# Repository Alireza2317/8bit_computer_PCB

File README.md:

# PCB Design of Ben Eater's 8-Bit Computer 🖥️

A complete **Printed Circuit Board (PCB)** implementation of the famous 8-bit computer architecture (SAP-1) designed by Ben Eater.

Moving from breadboards to a production-ready PCB, this project demonstrates complex signal routing, hierarchical schematic organization, and digital logic design using the **74xx TTL series** chips.

## 📸 3D Render

## ⚙️ Technical Specifications
| Feature | Details |
| :--- | :--- |
| **EDA Software** | KiCad |
| **Architecture** | Simple As Possible |
| **Logic Family** | 74LS / 74HC Series (TTL) |
| **PCB Layers** | 2 Layers |
| **Mounting** | Through-Hole Technology (THT) |

## 🧠 Design Challenges & Features
* **Hierarchical Schematics:** The design is broken down into modular logical blocks (Clock, RAM, ALU, Control Logic) using KiCad's hierarchical sheets for maintainability.
* **Complex Routing:** Managing hundreds of data and control lines on a 2-layer board required careful optimization of trace paths to minimize vias and ensure signal integrity.
* **Bus Architecture:** Implements a central 8-bit bus connecting all registers and the Arithmetic Logic Unit.

## 🖼️ Gallery

#### PCB Layout

#### 3d View Snapshot

### Schematics (Sneak Peek)

#### Root schematic page

#### RAM Module

## 🚀 How to Open
1. **Clone the repository:**
   ```bash
   git clone https://github.com/Alireza2317/8bit_computer_PCB
   ```
2. **Open in KiCad:**
   * Launch **KiCad**.
   * Go to `File > Open Project`.
   * Select the `.kicad_pro` file in the root directory.
3. **Explore:**
   * Click the **Schematic Editor** to see the logic.
   * Click the **PCB Editor** to see the physical routing.

## 👏 Acknowledgments
This project is based on the incredible educational series by **Ben Eater**.
* [Ben Eater's Website](https://eater.net/8bit)
* [YouTube Playlist](https://www.youtube.com/playlist?list=PLowKtXNTBypGqImE405J2565dvjafglHU)

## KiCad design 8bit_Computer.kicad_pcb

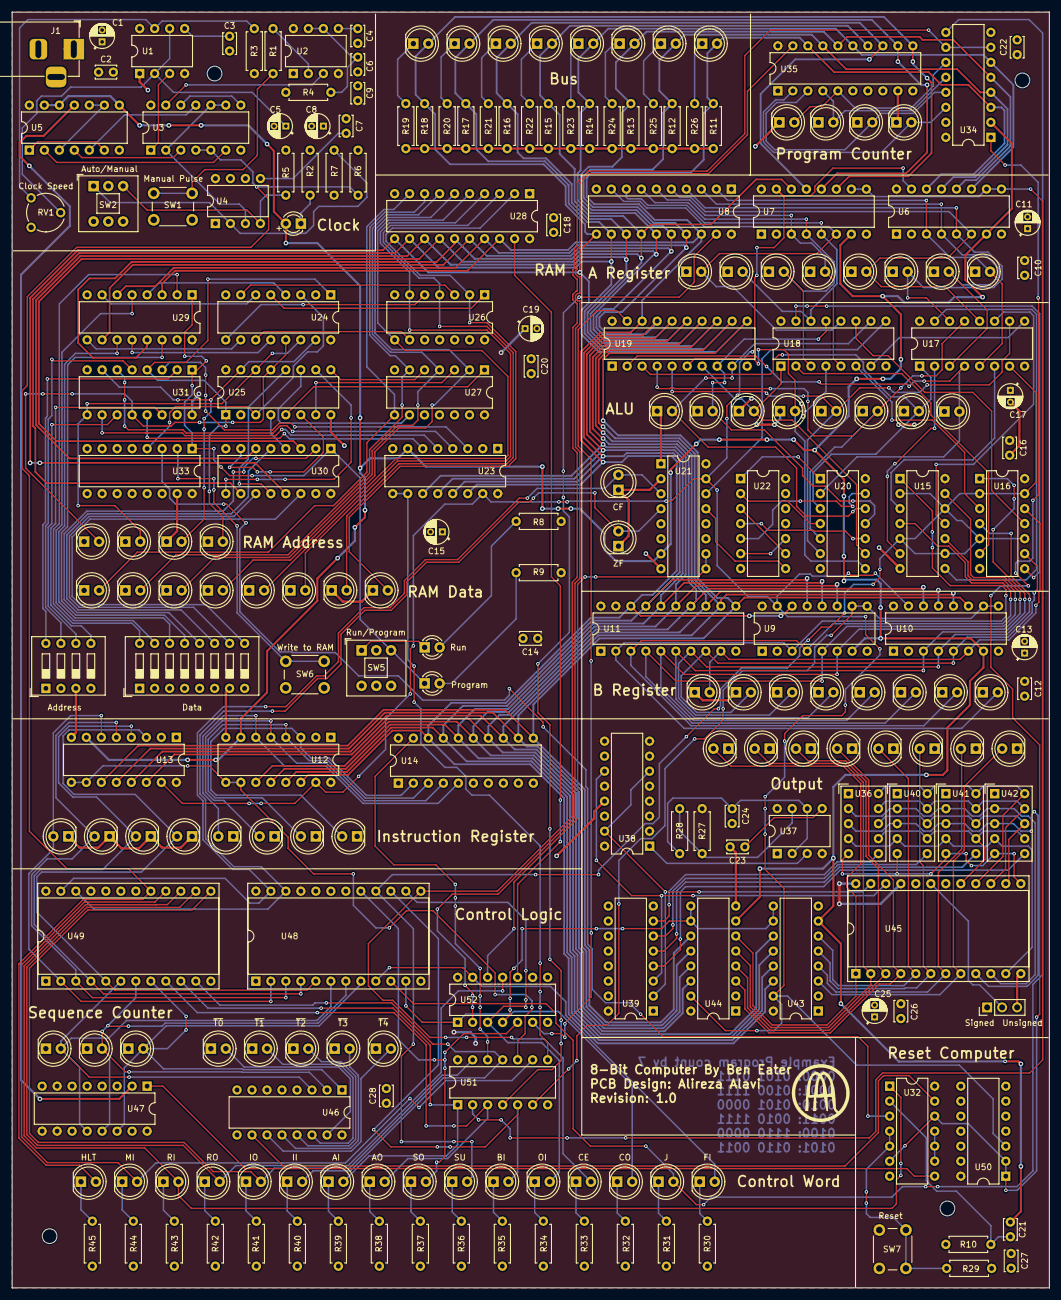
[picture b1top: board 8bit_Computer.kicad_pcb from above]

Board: 2 copper layers, 175.6 x 216.0 mm, 232 parts (0 on the bottom side), 231 nets.

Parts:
C1, C5: 100nF; CP_Radial_D4.0mm_P2.00mm
C2, C9, C14, C16, C18, C21: 1uF; C_Disc_D3.4mm_W2.1mm_P2.50mm
C3, C4, C7, C10, C12, C20, C22, C23, C24, C26, C27, C28: 10nF; C_Disc_D3.4mm_W2.1mm_P2.50mm
C6: 100nF; C_Disc_D3.4mm_W2.1mm_P2.50mm
C8: 2.2uF; CP_Radial_D4.0mm_P2.00mm
C11, C15, C17, C19: 10nF; CP_Radial_D4.0mm_P2.00mm
C13, C25: 1uF; CP_Radial_D4.0mm_P2.00mm
D1: bus7; LED_D3.0mm
D2: bus6; LED_D5.0mm
D3: bus5; LED_D5.0mm
D4: bus4; LED_D5.0mm
D5: bus3; LED_D5.0mm
D6: bus2; LED_D5.0mm
D7: bus1; LED_D5.0mm
D8: bus0; LED_D5.0mm
D9: pc3; LED_D5.0mm
D10: pc2; LED_D5.0mm
D11: pc1; LED_D5.0mm
D12: pc0; LED_D5.0mm
D13: Clock LED; LED_D5.0mm
D14: a7; LED_D5.0mm
D15: a6; LED_D5.0mm
D16: a5; LED_D5.0mm
D17: a4; LED_D5.0mm
D18: a3; LED_D5.0mm
D19: a2; LED_D5.0mm
D20: a0; LED_D5.0mm
D21: a1; LED_D5.0mm
D22: s7; LED_D5.0mm
D23: s5; LED_D5.0mm
D24: s6; LED_D5.0mm
D25: s4; LED_D5.0mm
D26: s3; LED_D5.0mm
D27: s2; LED_D5.0mm
D28: s1; LED_D5.0mm
D29: s0; LED_D5.0mm
D30: CF; LED_D5.0mm
D31: ra3; LED_D5.0mm
D32: ra2; LED_D5.0mm
D33: ra0; LED_D5.0mm
D34: ra1; LED_D5.0mm
D35: ZF; LED_D5.0mm
D36: r7; LED_D5.0mm
D37: r6; LED_D5.0mm
D38: r4; LED_D5.0mm
D39: r5; LED_D5.0mm
D40: r3; LED_D5.0mm
D41: r2; LED_D5.0mm
D42: r0; LED_D5.0mm
D43: r1; LED_D5.0mm
D44: Run; LED_D5.0mm
D45: Program; LED_D5.0mm
D46: b6; LED_D5.0mm
D47: b7; LED_D5.0mm
D48: b5; LED_D3.0mm
D49: b4; LED_D3.0mm
D50: b2; LED_D5.0mm
D51: b3; LED_D5.0mm
D52: b0; LED_D5.0mm
D53: b1; LED_D5.0mm
D54: out7; LED_D5.0mm
D55: out6; LED_D5.0mm
D56: out5; LED_D5.0mm
D57: out3; LED_D5.0mm
D58: out4; LED_D5.0mm
D59: out2; LED_D5.0mm
D60: out1; LED_D5.0mm
D61: out0; LED_D5.0mm
D62: ir7; LED_D5.0mm
D63: ir6; LED_D5.0mm
D64: ir5; LED_D5.0mm
D65: ir3; LED_D5.0mm
D66: ir4; LED_D5.0mm
D67: ir2; LED_D5.0mm
D68: ir1; LED_D5.0mm
D69: ir0; LED_D5.0mm
D70: sc1; LED_D5.0mm
D71: sc2; LED_D5.0mm
D72: sc0; LED_D5.0mm
D73: T0; LED_D5.0mm
D74: T2; LED_D5.0mm
D75: T1; LED_D5.0mm
D76: T4; LED_D5.0mm
D77: T3; LED_D5.0mm
D78: HLT; LED_D5.0mm
D79: MAR_In; LED_D5.0mm
D80: RAM_In; LED_D5.0mm
D81: RAM_Out; LED_D5.0mm
D82: IR_Out; LED_D5.0mm
D83: IR_In; LED_D5.0mm
D84: A_Out; LED_D5.0mm
D85: A_In; LED_D5.0mm
D86: Sum_Out; LED_D5.0mm
D87: Subtract; LED_D5.0mm
D88: Out_In; LED_D5.0mm
D89: B_In; LED_D5.0mm
D90: PC_En; LED_D5.0mm
D91: PC_Out; LED_D5.0mm
D92: Jump; LED_D5.0mm
D93: Flags_In; LED_D5.0mm
J1: DC Input; BarrelJack_Horizontal
J2: Sign Mode Jumper; PinHeader_1x03_P2.54mm_Vertical
M1, M2, M3, M4: MountingHole_2.5mm
R1, R3, R20, R22, R27: 1K; R_Axial_DIN0207_L6.3mm_D2.5mm_P7.62mm_Horizontal
R2: 1M; R_Axial_DIN0207_L6.3mm_D2.5mm_P7.62mm_Horizontal
R4, R5, R7, R9, R11, R13, R16, R19: 100; R_Axial_DIN0207_L6.3mm_D2.5mm_P7.62mm_Horizontal
R6, R8, R10, R12, R14, R15, R17, R18, R23, R44: 10K; R_Axial_DIN0207_L6.3mm_D2.5mm_P7.62mm_Horizontal
R21, R24, R25, R28, R29, R30, R31, R32, R33, R34, R35, R36, R37, R38, R39, R40, R41, R42, R43: 330; R_Axial_DIN0207_L6.3mm_D2.5mm_P7.62mm_Horizontal
R26: 100K; R_Axial_DIN0207_L6.3mm_D2.5mm_P7.62mm_Horizontal
R45: 1k; R_Axial_DIN0207_L6.3mm_D2.5mm_P7.62mm_Horizontal
RV1: 100K; Potentiometer_Piher_PT-6-V_Vertical
SW1: Clock Mode Switch; SW_PUSH_6mm
SW2: Manual Pulse; SW_Push_2P2T_Toggle_CK_PVA2OAH5xxxxxxV2
SW3: Program Address; SW_DIP_SPSTx04_Slide_9.78x12.34mm_W7.62mm_P2.54mm
SW4: Program Data; SW_DIP_SPSTx08_Slide_9.78x22.5mm_W7.62mm_P2.54mm
SW5: Program Button; SW_Push_2P2T_Toggle_CK_PVA2OAH5xxxxxxV2
SW6: Program/Run Mode Switch; SW_PUSH_6mm
SW7: Reset Button; SW_PUSH_6mm
U1, U2: NE555P; DIP-8_W7.62mm
U3: 74LS245; DIP-14_W7.62mm
U4: 74LS00; DIP-8_W7.62mm
U5, U50, U52: 74LS00; DIP-14_W7.62mm
U6, U9, U18, U29, U34: 74LS245; DIP-16_W7.62mm
U7, U47: 74LS161; DIP-16_W7.62mm
U8: NE555P; DIP-20_W7.62mm
U10, U23, U24, U30, U31, U33, U44: 74LS173; DIP-16_W7.62mm
U11: 74LS173; DIP-20_W7.62mm
U12, U21: 74LS157; DIP-16_W7.62mm
U13: 74LS189; DIP-16_W7.62mm
U14: 74LS04; DIP-20_W7.62mm
U15: 74LS189; DIP-14_W7.62mm
U16, U22: 74LS157; DIP-14_W7.62mm
U17: 74LS04; DIP-16_W7.62mm
U19: 74LS283; DIP-20_W7.62mm
U20: 74LS283; DIP-14_W7.62mm
U25: 74LS08; DIP-16_W7.62mm
U26: 74LS02; DIP-14_W7.62mm
U27: 74LS86; DIP-14_W7.62mm
U28: 74LS86; DIP-20_W7.62mm
U32: 74LS173; DIP-14_W7.62mm
U35: 74LS76; DIP-20_W7.62mm
U36: NE555D; HDSP-7401
U37: Hundred's Place; DIP-8_W7.62mm
U38: Minus Sign; DIP-16_W7.62mm
U39: Ten's Place; DIP-16_W7.62mm
U40: One's Place; HDSP-7401
U41, U42: 28c16; HDSP-7401
U43: 74LS139; DIP-16_W7.62mm
U45: 74LS173; DIP-24_W15.24mm_Socket
U46: 28c16; DIP-16_W7.62mm
U48: 74LS138; DIP-24_W15.24mm_Socket
U49: 74LS06; DIP-24_W15.24mm_Socket
U51: 74LS06; DIP-14_W7.62mm

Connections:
/A Register/a0: D9.2 (A), U6.3 (Q0), U8.2 (A0), U17.5 (A1)
/A Register/a1: D8.2 (A), U6.4 (Q1), U8.3 (A1), U17.3 (A2)
/A Register/a2: D7.2 (A), U6.5 (Q2), U8.4 (A2), U17.14 (A3)
/A Register/a3: D6.2 (A), U6.6 (Q3), U8.5 (A3), U17.12 (A4)
/A Register/a4: D5.2 (A), U7.3 (Q0), U8.6 (A4), U18.5 (A1)
/A Register/a5: D4.2 (A), U7.4 (Q1), U8.7 (A5), U18.3 (A2)
/A Register/a6: D3.2 (A), U7.5 (Q2), U8.8 (A6), U18.14 (A3)
/A Register/a7: D2.2 (A), U7.6 (Q3), U8.9 (A7), U18.12 (A4)
/ALU/Flags Register/zero_bit: U21.13 (D1), U22.8
/ALU/bc0: U15.3, U17.6 (B1)
/ALU/bc1: U15.6, U17.2 (B2)
/ALU/bc2: U15.8, U17.15 (B3)
/ALU/bc3: U15.11, U17.11 (B4)
/ALU/bc4: U16.3, U18.6 (B1)
/ALU/bc5: U16.6, U18.2 (B2)
/ALU/bc6: U16.8, U18.15 (B3)
/ALU/bc7: U16.11, U18.11 (B4)
/ALU/carry_bit: U18.9 (C4), U21.14 (D0)
/ALU/middle_carry: U17.9 (C4), U18.7 (C0)
/ALU/s0: D33.2 (A), U17.4 (S1), U19.2 (A0), U20.2
/ALU/s1: D32.2 (A), U17.1 (S2), U19.3 (A1), U20.3
/ALU/s2: D31.2 (A), U17.13 (S3), U19.4 (A2), U20.5
/ALU/s3: D30.2 (A), U17.10 (S4), U19.5 (A3), U20.6
/ALU/s4: D29.2 (A), U18.4 (S1), U19.6 (A4), U20.8
/ALU/s5: D28.2 (A), U18.1 (S2), U19.7 (A5), U20.9
/ALU/s6: D27.2 (A), U18.13 (S3), U19.8 (A6), U20.11
/ALU/s7: D26.2 (A), U18.10 (S4), U19.9 (A7), U20.12
/B Register/b0: D17.2 (A), U9.3 (Q0), U11.2 (A0), U15.1
/B Register/b1: D16.2 (A), U9.4 (Q1), U11.3 (A1), U15.4
/B Register/b2: D15.2 (A), U9.5 (Q2), U11.4 (A2), U15.10
/B Register/b3: D14.2 (A), U9.6 (Q3), U11.5 (A3), U15.13
/B Register/b4: D13.2 (A), U10.3 (Q0), U11.6 (A4), U16.1
/B Register/b5: D12.2 (A), U10.4 (Q1), U11.7 (A5), U16.4
/B Register/b6: D11.2 (A), U10.5 (Q2), U11.8 (A6), U16.9
/B Register/b7: D10.2 (A), U10.6 (Q3), U11.9 (A7), U16.12
/Clock Module/AO: U1.3 (Q), U3.1
/Clock Module/MO: U2.3 (Q), U3.13
/Clock Module/select clock mode: U3.2, U3.9, U3.10, U4.3 (Q)
/Control Logic/sc0: D75.2 (A), U46.1 (A0), U47.14 (Q0), U48.8 (A0), U49.8 (A0)
/Control Logic/sc1: D73.2 (A), U46.2 (A1), U47.13 (Q1), U48.7 (A1), U49.7 (A1)
/Control Logic/sc2: D71.2 (A), U46.3 (A2), U47.12 (Q2), U48.6 (A2), U49.6 (A2)
/Control Logic/~T0: D70.2 (A), U46.15 (O0)
/Control Logic/~T1: D72.2 (A), U46.14 (O1)
/Control Logic/~T2: D74.2 (A), U46.13 (O2)
/Control Logic/~T3: D76.2 (A), U46.12 (O3)
/Control Logic/~T4: D77.2 (A), U46.11 (O4)
/Control Logic/~T5: U32.13, U46.10 (O5)
/Control Logic/~sq_mr: U32.8, U47.1 (~MR)
/Display/a: U36.10 (A), U40.10 (A), U41.10 (A), U42.10 (A), U45.16 (I/O6)
/Display/b: U36.9 (B), U40.9 (B), U41.9 (B), U42.9 (B), U45.15 (I/O5)
/Display/c: U36.8 (C), U40.8 (C), U41.8 (C), U42.8 (C), U45.14 (I/O4)
/Display/d: U36.5 (D), U40.5 (D), U41.5 (D), U42.5 (D), U45.13 (I/O3)
/Display/dp: U36.7 (DP), U40.7 (DP), U41.7 (DP), U42.7 (DP), U45.17 (I/O7)
/Display/e: U36.4 (E), U40.4 (E), U41.4 (E), U42.4 (E), U45.11 (I/O2)
/Display/f: U36.2 (F), U40.2 (F), U41.2 (F), U42.2 (F), U45.10 (I/O1)
/Display/g: U36.3 (G), U40.3 (G), U41.3 (G), U42.3 (G), U45.9 (I/O0)
/Display/hundreds: U39.6 (O2), U40.6 (CC)
/Display/mc0: U38.6 (C), U38.15 (Q), U39.2 (A0), U45.23 (A8)
/Display/mc1: U38.11 (Q), U39.3 (A1), U45.22 (A9)
/Display/mux_clock: U37.3 (Q), U38.1 (C)
/Display/ones: U39.4 (O0), U42.6 (CC)
/Display/out0: D69.2 (A), U43.3 (Q0), U45.8 (A0)
/Display/out1: D68.2 (A), U43.4 (Q1), U45.7 (A1)
/Display/out2: D67.2 (A), U43.5 (Q2), U45.6 (A2)
/Display/out3: D66.2 (A), U43.6 (Q3), U45.5 (A3)
/Display/out4: D65.2 (A), U44.3 (Q0), U45.4 (A4)
/Display/out5: D64.2 (A), U44.4 (Q1), U45.3 (A5)
/Display/out6: D63.2 (A), U44.5 (Q2), U45.2 (A6)
/Display/out7: D62.2 (A), U44.6 (Q3), U45.1 (A7)
/Display/sign: U36.6 (CC), U39.7 (O3)
/Display/tens: U39.5 (O1), U41.6 (CC)
/Instruction Register/ir0: D25.2 (A), U12.3 (Q0), U14.2 (A0)
/Instruction Register/ir1: D24.2 (A), U12.4 (Q1), U14.3 (A1)
/Instruction Register/ir2: D23.2 (A), U12.5 (Q2), U14.4 (A2)
/Instruction Register/ir3: D22.2 (A), U12.6 (Q3), U14.5 (A3)
/Instruction Register/ir4: D21.2 (A), U13.3 (Q0), U48.5 (A3), U49.5 (A3)
/Instruction Register/ir5: D20.2 (A), U13.4 (Q1), U48.4 (A4), U49.4 (A4)
/Instruction Register/ir6: D19.2 (A), U13.5 (Q2), U48.3 (A5), U49.3 (A5)
/Instruction Register/ir7: D18.2 (A), U13.6 (Q3), U48.2 (A6), U49.2 (A6)
/Program Counter/pc0: D53.2 (A), U34.14 (Q0), U35.2 (A0)
/Program Counter/pc1: D52.2 (A), U34.13 (Q1), U35.3 (A1)
/Program Counter/pc2: D51.2 (A), U34.12 (Q2), U35.4 (A2)
/Program Counter/pc3: D50.2 (A), U34.11 (Q3), U35.5 (A3)
/RAM/Computer Mode Switcher/di0: U24.4 (D1), U29.4 (Za)
/RAM/Computer Mode Switcher/di1: U24.6 (D2), U29.7 (Zb)
/RAM/Computer Mode Switcher/di2: U24.10 (D3), U29.9 (Zc)
/RAM/Computer Mode Switcher/di3: U24.12 (D4), U29.12 (Zd)
/RAM/Computer Mode Switcher/di4: U25.4 (D1), U30.4 (Za)
/RAM/Computer Mode Switcher/di5: U25.6 (D2), U30.7 (Zb)
/RAM/Computer Mode Switcher/di6: U25.10 (D3), U30.9 (Zc)
/RAM/Computer Mode Switcher/di7: U25.12 (D4), U30.12 (Zd)
/RAM/Computer Mode Switcher/mar0: U23.3 (Q0), U31.3 (I1a)
/RAM/Computer Mode Switcher/mar1: U23.4 (Q1), U31.6 (I1b)
/RAM/Computer Mode Switcher/mar2: U23.5 (Q2), U31.10 (I1c)
/RAM/Computer Mode Switcher/mar3: U23.6 (Q3), U31.13 (I1d)
/RAM/Computer Mode Switcher/pa0: SW3.8, U31.2 (I0a)
/RAM/Computer Mode Switcher/pa1: SW3.7, U31.5 (I0b)
/RAM/Computer Mode Switcher/pa2: SW3.6, U31.11 (I0c)
/RAM/Computer Mode Switcher/pa3: SW3.5, U31.14 (I0d)
/RAM/Computer Mode Switcher/pd0: SW4.16, U29.2 (I0a)
/RAM/Computer Mode Switcher/pd1: SW4.15, U29.5 (I0b)
/RAM/Computer Mode Switcher/pd2: SW4.14, U29.11 (I0c)
/RAM/Computer Mode Switcher/pd3: SW4.13, U29.14 (I0d)
/RAM/Computer Mode Switcher/pd4: SW4.12, U30.2 (I0a)
/RAM/Computer Mode Switcher/pd5: SW4.11, U30.5 (I0b)
/RAM/Computer Mode Switcher/pd6: SW4.10, U30.11 (I0c)
/RAM/Computer Mode Switcher/pd7: SW4.9, U30.14 (I0d)
/RAM/Computer Mode Switcher/select r/p: D49.1 (K), SW5.3 (C), U29.1 (S), U30.1 (S), U31.1 (S), U33.1 (S)
/RAM/Computer Mode Switcher/~RAM_WE: U24.3 (~WE), U25.3 (~WE), U33.4 (Za)
/RAM/a0: D39.2 (A), U24.1 (A0), U25.1 (A0), U31.4 (Za)
/RAM/a1: D38.2 (A), U24.15 (A1), U25.15 (A1), U31.7 (Zb)
/RAM/a2: D37.2 (A), U24.14 (A2), U25.14 (A2), U31.9 (Zc)
/RAM/a3: D36.2 (A), U24.13 (A3), U25.13 (A3), U31.12 (Zd)
/RAM/r0: D47.2 (A), U26.2, U28.2 (A0)
/RAM/r1: D46.2 (A), U26.4, U28.3 (A1)
/RAM/r2: D45.2 (A), U26.6, U28.4 (A2)
/RAM/r3: D44.2 (A), U26.8, U28.5 (A3)
/RAM/r4: D43.2 (A), U27.2, U28.6 (A4)
/RAM/r5: D42.2 (A), U27.4, U28.7 (A5)
/RAM/r6: D41.2 (A), U27.6, U28.8 (A6)
/RAM/r7: D40.2 (A), U27.8, U28.9 (A7)
A_In: D87.2 (A), U49.10 (I/O1), U51.1
A_Out: D86.2 (A), U49.9 (I/O0), U51.3
B_In: D83.2 (A), U48.15 (I/O5), U51.5
Bus0: D61.2 (A), R11.1, U6.14 (D0), U8.18 (B0), U9.14 (D0), U11.18 (B0), U12.14 (D0), U14.18 (B0), U19.18 (B0), U23.14 (D0), U28.18 (B0), U29.3 (I1a), U34.3 (D0), U35.18 (B0), U43.14 (D0)
Bus1: D60.2 (A), R12.1, U6.13 (D1), U8.17 (B1), U9.13 (D1), U11.17 (B1), U12.13 (D1), U14.17 (B1), U19.17 (B1), U23.13 (D1), U28.17 (B1), U29.6 (I1b), U34.4 (D1), U35.17 (B1), U43.13 (D1)
Bus2: D59.2 (A), R13.1, U6.12 (D2), U8.16 (B2), U9.12 (D2), U11.16 (B2), U12.12 (D2), U14.16 (B2), U19.16 (B2), U23.12 (D2), U28.16 (B2), U29.10 (I1c), U34.5 (D2), U35.16 (B2), U43.12 (D2)
Bus3: D58.2 (A), R14.1, U6.11 (D3), U8.15 (B3), U9.11 (D3), U11.15 (B3), U12.11 (D3), U14.15 (B3), U19.15 (B3), U23.11 (D3), U28.15 (B3), U29.13 (I1d), U34.6 (D3), U35.15 (B3), U43.11 (D3)
Bus4: D57.2 (A), R15.1, U7.14 (D0), U8.14 (B4), U10.14 (D0), U11.14 (B4), U13.14 (D0), U14.14 (B4), U19.14 (B4), U28.14 (B4), U30.3 (I1a), U35.14 (B4), U44.14 (D0)
Bus5: D56.2 (A), R16.1, U7.13 (D1), U8.13 (B5), U10.13 (D1), U11.13 (B5), U13.13 (D1), U14.13 (B5), U19.13 (B5), U28.13 (B5), U30.6 (I1b), U35.13 (B5), U44.13 (D1)
Bus6: D55.2 (A), R17.1, U7.12 (D2), U8.12 (B6), U10.12 (D2), U11.12 (B6), U13.12 (D2), U14.12 (B6), U19.12 (B6), U28.12 (B6), U30.10 (I1c), U35.12 (B6), U44.12 (D2)
Bus7: D54.2 (A), R18.1, U7.11 (D3), U8.11 (B7), U10.11 (D3), U11.11 (B7), U13.11 (D3), U14.11 (B7), U19.11 (B7), U28.11 (B7), U30.13 (I1d), U35.11 (B7), U44.11 (D3)
CF: D35.2 (A), U21.3 (Q0), U48.23 (A8), U49.23 (A8)
Clock: C21.1, D1.2 (A), U5.8, U5.12, U5.13, U6.7 (Cp), U7.7 (Cp), U9.7 (Cp), U10.7 (Cp), U12.7 (Cp), U13.7 (Cp), U21.7 (Cp), U23.7 (Cp), U34.2 (CP), U43.7 (Cp), U44.7 (Cp)
Flags_In: D78.2 (A), U48.9 (I/O0), U52.13
GND: C1.2, C2.1, C3.1, C4.1, C5.2, C6.1, C7.1, C8.2, C9.1, C10.2, C11.2, C12.2, C13.2, C14.2, C15.2, C16.2, C17.2, C18.2, C19.2, C20.2, C22.2, C23.2, C24.2, C25.2, C26.2, C27.2, C28.2, D2.1 (K), D3.1 (K), D4.1 (K), D5.1 (K), D6.1 (K), D7.1 (K), D8.1 (K), D9.1 (K), D10.1 (K), D11.1 (K), D12.1 (K), D13.1 (K), D14.1 (K), D15.1 (K), D16.1 (K), D17.1 (K), D18.1 (K), D19.1 (K), D20.1 (K), D21.1 (K), D22.1 (K), D23.1 (K), D24.1 (K), D25.1 (K), D26.1 (K), D27.1 (K), D28.1 (K), D29.1 (K), D30.1 (K), D31.1 (K), D32.1 (K), D33.1 (K), D34.1 (K), D35.1 (K), D36.1 (K), D37.1 (K), D38.1 (K), D39.1 (K), D40.1 (K), D41.1 (K), D42.1 (K), D43.1 (K), D44.1 (K), D45.1 (K), D46.1 (K), D47.1 (K), D50.1 (K), D51.1 (K), D52.1 (K), D53.1 (K), D62.1 (K), D63.1 (K), D64.1 (K), D65.1 (K), D66.1 (K), D67.1 (K), D68.1 (K), D69.1 (K), D70.1 (K), D71.1 (K), D72.1 (K), D73.1 (K), D74.1 (K), D75.1 (K), D76.1 (K), D77.1 (K), J1.2, J2.3, R2.2, R6.2, R10.2, R11.2, R12.2, R13.2, R14.2, R15.2, R16.2, R17.2, R18.2, R19.2, R20.2, R21.2, R22.2, R23.2, R24.2, R25.2, R26.2, R29.2, R30.2, R31.2, R32.2, R33.2, R34.2, R35.2, R36.2, R37.2, R38.2, R39.2, R40.2, R41.2, R42.2, R43.2, R44.2, R45.2, SW1.1, SW2.2 (B), SW3.1, SW3.2, SW3.3, SW3.4, SW4.1, SW4.2, SW4.3, SW4.4, SW4.5, SW4.6, SW4.7, SW4.8, SW5.2 (B), SW6.1, U1.1 (GND), U2.1 (GND), U3.7 (GND), U4.1 (GND), U4.6 (THR), U5.7 (GND), U6.1 (Oe1), U6.2 (Oe2), U6.8 (GND), U7.1 (Oe1), U7.2 (Oe2), U7.8 (GND), U8.10 (GND), U9.1 (Oe1), U9.2 (Oe2), U9.8 (GND), U10.1 (Oe1), U10.2 (Oe2), U10.8 (GND), U11.10 (GND), U12.1 (Oe1), U12.2 (Oe2), U12.8 (GND), U13.1 (Oe1), U13.2 (Oe2), U13.8 (GND), U14.6 (A4), U14.7 (A5), U14.8 (A6), U14.9 (A7), U14.10 (GND), U15.7 (GND), U16.7 (GND), U17.8 (GND), U18.8 (GND), U19.10 (GND), U20.7 (GND), U21.1 (Oe1), U21.2 (Oe2), U21.8 (GND), U22.7 (GND), U23.1 (Oe1), U23.2 (Oe2), U23.8 (GND), U24.2 (~CS), U24.8 (GND), U25.2 (~CS), U25.8 (GND), U26.7 (GND), U27.7 (GND), U28.10 (GND), U29.8 (GND), U29.15 (E), U30.8 (GND), U30.15 (E), U31.8 (GND), U31.15 (E), U32.7 (GND), U33.8 (GND), U33.15 (E), U34.8 (GND), U35.6 (A4), U35.7 (A5), U35.8 (A6), U35.9 (A7), U35.10 (GND), U37.1 (GND), U38.13 (GND), U39.1 (E), U39.8 (GND), U43.1 (Oe1), U43.2 (Oe2), U43.8 (GND), U44.1 (Oe1), U44.2 (Oe2), U44.8 (GND), U45.12 (GND), U45.18 (~CE), U45.20 (~OE), U46.4 (E1), U46.5 (E2), U46.8 (GND), U47.8 (GND), U48.12 (GND), U48.18 (~CE), U48.19 (A10), U48.20 (~OE), U49.1 (A7), U49.12 (GND), U49.18 (~CE), U49.19 (A10), U49.20 (~OE), U50.7 (GND), U51.7 (GND), U52.7 (GND)
HLT: D93.2 (A), R6.1, U3.4, U3.5, U49.17 (I/O7)
IR_In: D88.2 (A), U49.11 (I/O2), U51.11
IR_Out: D89.2 (A), U49.13 (I/O3), U51.13
Inverted Clock: U5.11, U47.2 (CP)
Jump: D79.2 (A), U34.9 (~PE), U48.10 (I/O1)
MAR_In: D92.2 (A), U49.16 (I/O6), U51.9
unnamed: C21.2, R10.1, U32.2
unnamed: D1.1 (K), R2.1
unnamed: D48.2 (A), R8.2
unnamed: D48.1 (K), SW5.1 (A)
unnamed: D49.2 (A), R9.2
unnamed: D54.1 (K), R19.1
unnamed: D55.1 (K), R20.1
unnamed: D56.1 (K), R21.1
unnamed: D57.1 (K), R22.1
unnamed: D58.1 (K), R23.1
unnamed: D59.1 (K), R24.1
unnamed: D60.1 (K), R25.1
unnamed: D61.1 (K), R26.1
unnamed: D78.1 (K), R30.1
unnamed: D79.1 (K), R31.1
unnamed: D80.1 (K), R32.1
unnamed: D81.1 (K), R33.1
unnamed: D82.1 (K), R34.1
unnamed: D83.1 (K), R35.1
unnamed: D84.1 (K), R36.1
unnamed: D85.1 (K), R37.1
unnamed: D86.1 (K), R38.1
unnamed: D87.1 (K), R39.1
unnamed: D88.1 (K), R40.1
unnamed: D89.1 (K), R41.1
unnamed: D90.1 (K), R42.1
unnamed: D91.1 (K), R43.1
unnamed: D92.1 (K), R44.1
unnamed: D93.1 (K), R45.1
unnamed: R1.2, SW1.2
unnamed: R29.1, SW7.2, U32.4, U32.5
unnamed: C3.2, U1.5 (CV)
unnamed: R3.2, RV1.3, U1.7 (DIS)
unnamed: C5.1, RV1.2, U1.2 (TR), U1.6 (THR)
unnamed: C4.2, U2.5 (CV)
unnamed: C6.2, R4.2, U2.6 (THR), U2.7 (DIS)
unnamed: R1.1, U2.2 (TR)
unnamed: U3.3, U5.4
unnamed: U3.6, U5.2
unnamed: U3.11, U5.5
unnamed: U3.8, U3.12
unnamed: C7.2, U4.5 (CV)
unnamed: R5.2, SW2.3 (C), U4.4 (R)
unnamed: R7.2, SW2.1 (A), U4.2 (TR)
unnamed: U5.1, U5.6
unnamed: U5.3, U5.9, U5.10
unnamed: U20.1, U22.1
unnamed: U20.4, U22.2
unnamed: U20.10, U22.4
unnamed: U20.13, U22.5
unnamed: U22.3, U22.9
unnamed: U22.6, U22.10
unnamed: U24.5 (~Q0), U26.1
unnamed: U24.7 (~Q1), U26.3
unnamed: U24.9 (~Q2), U26.5
unnamed: U24.11 (~Q3), U26.9
unnamed: U25.5 (~Q0), U27.1
unnamed: U25.7 (~Q1), U27.3
unnamed: U25.9 (~Q2), U27.5
unnamed: U25.11 (~Q3), U27.9
unnamed: U32.9, U32.10, U32.11
unnamed: SW6.2, U33.2 (I0a)
unnamed: U32.3, U33.3 (I1a)
unnamed: C23.1, U37.5 (CV)
unnamed: R27.2, R28.1, U37.7 (DIS)
unnamed: C24.1, R28.2, U37.2 (TR), U37.6 (THR)
Out_In: D82.2 (A), U48.14 (I/O4), U52.3
PC_En: D81.2 (A), U34.7 (CEP), U34.10 (CET), U48.13 (I/O3)
PC_Out: D80.2 (A), U48.11 (I/O2), U52.1
RAM_In: D91.2 (A), U32.1, U49.15 (I/O5)
RAM_Out: D90.2 (A), U49.14 (I/O4), U52.11
RESET_SIGNAL: U6.15 (Mr), U7.15 (Mr), U9.15 (Mr), U10.15 (Mr), U12.15 (Mr), U13.15 (Mr), U21.15 (Mr), U23.15 (Mr), U43.15 (Mr), U44.15 (Mr), U50.3
Sign Mode: J2.2, U45.19 (A10)
Subtract: D84.2 (A), U15.2, U15.5, U15.9, U15.12, U16.2, U16.5, U16.10, U16.13, U17.7 (C0), U48.16 (I/O6)
Sum_Out: D85.2 (A), U48.17 (I/O7), U52.5
VCC: C1.1, C2.2, C8.1, C9.2, C10.1, C11.1, C12.1, C13.1, C14.1, C15.1, C16.1, C17.1, C18.1, C19.1, C20.1, C22.1, C25.1, C26.1, C27.1, C28.1, J1.1, J2.1, R3.1, R4.1, R5.1, R7.1, R8.1, R9.1, R27.1, SW7.1, U1.4 (R), U1.8 (VCC), U2.4 (R), U2.8 (VCC), U3.14 (VCC), U4.8 (VCC), U5.14 (VCC), U6.16 (VCC), U7.16 (VCC), U8.1 (A->B), U8.20 (VCC), U9.16 (VCC), U10.16 (VCC), U11.1 (A->B), U11.19 (CE), U11.20 (VCC), U12.16 (VCC), U13.16 (VCC), U14.1 (A->B), U14.20 (VCC), U15.14 (VCC), U16.14 (VCC), U17.16 (VCC), U18.16 (VCC), U19.1 (A->B), U19.20 (VCC), U20.14 (VCC), U21.16 (VCC), U22.14 (VCC), U23.16 (VCC), U24.16 (VCC), U25.16 (VCC), U26.14 (VCC), U27.14 (VCC), U28.1 (A->B), U28.20 (VCC), U29.16 (VCC), U30.16 (VCC), U31.16 (VCC), U32.14 (VCC), U33.16 (VCC), U34.16 (VCC), U35.1 (A->B), U35.20 (VCC), U37.4 (R), U37.8 (VCC), U38.2 (~S), U38.3 (~R), U38.4 (J), U38.5 (VCC), U38.7 (~S), U38.8 (~R), U38.9 (J), U38.12 (K), U38.16 (K), U39.16 (VCC), U43.16 (VCC), U44.16 (VCC), U45.21 (~WE), U45.24 (VCC), U46.6 (E3), U46.16 (VCC), U47.7 (CEP), U47.9 (~PE), U47.10 (CET), U47.16 (VCC), U48.1 (A7), U48.21 (~WE), U48.24 (VCC), U49.21 (~WE), U49.24 (VCC), U50.14 (VCC), U51.14 (VCC), U52.14 (VCC)
ZF: D34.2 (A), U21.4 (Q1), U48.22 (A9), U49.22 (A9)
~A_In: U6.9 (E1), U6.10 (E2), U7.9 (E1), U7.10 (E2), U51.2
~A_Out: U8.19 (CE), U51.4
~B_In: U9.9 (E1), U9.10 (E2), U10.9 (E1), U10.10 (E2), U51.6
~Flags_In: U21.9 (E1), U21.10 (E2), U52.12
~IR_In: U12.9 (E1), U12.10 (E2), U13.9 (E1), U13.10 (E2), U51.10
~IR_Out: U14.19 (CE), U51.12
~MAR_In: U23.9 (E1), U23.10 (E2), U51.8
~Out_In: U43.9 (E1), U43.10 (E2), U44.9 (E1), U44.10 (E2), U52.4
~PC_Out: U35.19 (CE), U52.2
~RAM_Out: U28.19 (CE), U52.10
~RESET_SIGNAL: U32.6, U32.12, U34.1 (~MR), U50.1, U50.2
~Sum_Out: U19.19 (CE), U52.6

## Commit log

2025-01-27 added all the project files
    also added the gerber zip file
2025-12-06 updated kicad version from 7 to 9!
2025-12-06 revised README

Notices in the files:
README.md:
License: MIT
